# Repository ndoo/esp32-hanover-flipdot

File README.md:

# ESP32 Hanover Flip-dot Sign Controller

This controller directly controls Hanover Displays Ltd. dot-boards CMOS logic hardware directly through the parallel 14-pin ribbon cable, without the Hanover 7070 or 7080 processor board.

## Design Considerations

This controller's design is based on [Damien Walsh's work on Hanover flip-dot signs](https://damow.net/fun-with-flip-dot-displays/), with only layout changes targeting PCB fabrication and assembly services.

The following considerations went into the PCB schematic and layout:

* SMT components used where possible
* All components are only on the top side of the PCB
* The ESP32-PICO-D4 SIP is used instead of a separate ESP32 module
* PCB size minimized to increase savings with panelization
* All board enable lines are connected to support up to 4 parallel dot-boards
* Generous use of ground stitching vias

## PCBA Notes

### Time/Money Saving

I strongly suggest removing the following items from the PCBA BoM, as they are generic 2.54mm through-hole parts and can be easily sourced at a local dealer:

* J2: CONN HEADER R/A 14POS 2.54MM
* J3: DIP Black Male Header VERT

### Dot-board Ribbon Cable

J2 is specified as a 2x7 pin 2.54mm pitch shrouded header for IDC cables, so a matching 2x7 pin 2.54mm pitch IDC connector must be retrofitted on the original Hanover dot-board ribbon cable.

The original Hanover cable is a Lumberg Micromodul series MICA 14 connector which mates to a corresponding MICS 14 header. As the Lumberg Micromodul parts are much harder to source (with the bottom line being that they cost more) and requires a custom footprint on the PCB, a jellybean part solution was preferred.

### Bill of Materials

The BOM CSV provided uses [Seeed Studio OPL](https://www.seeedstudio.com/opl.html) SKUs for jellybean parts as I have a personal preference for Seeed Studio's Fusion PCBA service. If using other PCBA services, please substitute the Seeed OPL SKUs accordingly.

## Firmware

Reference ESP32 Arduino framework firmware source is available at [ndoo/esp32-hanover-flipdot-firmware](https://github.com/ndoo/esp32-hanover-flipdot-firmware)

### ESP32 GPIO mapping

* Enable Display 1 - GPIO 15
* Enable Display 2 - GPIO 13
* Enable Display 3 - GPIO 12
* Enable Display 4 - GPIO 14
* Column Advance - GPIO 27
* Reset - GPIO 26
* Set/Unset - GPIO 25
* Row Advance - GPIO 33
* Coil Pulse - GPIO 2
* LED 1 - GPIO 23
* LED 2 - GPIO 19
* LED 3 - GPIO 22

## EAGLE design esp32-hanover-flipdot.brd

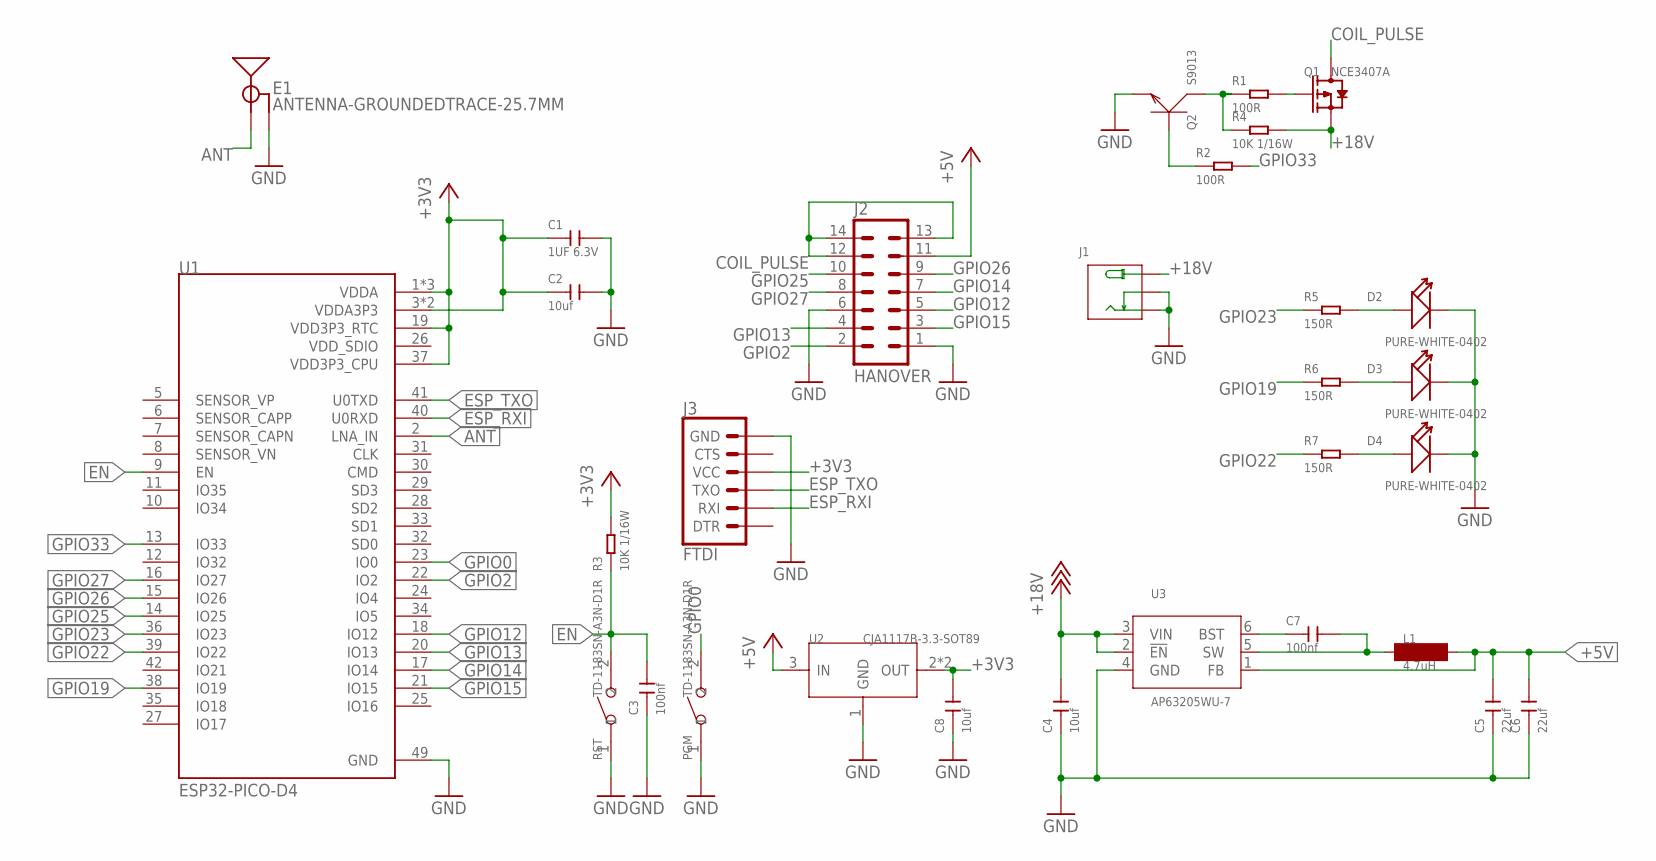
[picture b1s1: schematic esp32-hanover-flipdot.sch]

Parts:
C1: 1UF 6.3V; C0402
C2, C8: 10uf; C0402
C3, C7: 100nf; C0402
C4: 10uf; C0805
C5, C6: 22uf; C0805
D2, D3, D4: PURE-WHITE-0402; LED-0402
E1: ANTENNA-GROUNDEDTRACE-25.7MM; TRACE_ANTENNA_2.4GHZ_25.7MM
J1: DC-005; 3P-L14.2*W11.0*H9.0MM
J2: HANOVER; ML14
J3: FTDI; 6_PIN_SERIAL_TARGET_SIDE_W_SILK
L1: 4.7uH; INDC2016X100N
PGM: TD-1183SN-A3N-D1R; SW2-2.6-3.0X2.5X1.2+0.4MM
Q1: NCE3407A; SOT-23
Q2: S9013; SOT-23
R1, R2: 100R; R0402
R3, R4: 10K 1/16W; R0402
R5, R6, R7: 150R; R0402; MPN RC0402FR-07150RL
RST: TD-1183SN-A3N-D1R; SW2-2.6-3.0X2.5X1.2+0.4MM
U1: ESP32-PICO-D4; PQFN50P700X700X104-49N
U2: CJA1117B-3.3-SOT89; SOT-89
U3: AP63205WU-7; SOT95P280X100-6N

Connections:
+3V3: C1.1, C2.1, C8.2, J3.P$4 (VCC), R3.2, U1.1 (VDDA), U1.3 (VDDA3P3), U1.4 (VDDA3P3), U1.19 (VDD3P3_RTC), U1.37 (VDD3P3_CPU), U1.43 (VDDA), U1.46 (VDDA), U2.2 (OUT), U2.4 (OUT)
+5V: C5.2, C6.2, J2.11, L1.2, U2.3 (IN), U3.1 (FB)
+18V: C4.2, J1.+B (+), J1.+T (+), Q1.2 (S), R4.2, U3.2 (!EN), U3.3 (VIN)
ANT: E1.ANT (SIGNAL), U1.2 (LNA_IN)
COIL_PULSE: J2.12, J2.13, J2.14, Q1.3 (D)
EN: C3.2, R3.1, RST.2, U1.9 (EN)
ESP_RXI: J3.P$3 (RXI), U1.40 (U0RXD)
ESP_TXO: J3.P$2 (TXO), U1.41 (U0TXD)
GND: C1.2, C2.2, C3.1, C4.1, C5.1, C6.1, C8.1, D2.-, D3.-, D4.-, E1.GND, E1.GND2 (GND), J1.-1B (-), J1.-1T (-), J1.-2B (CDN), J1.-2T (CDN), J2.1, J2.6, J3.P$6 (GND), PGM.1, Q2.2 (E), RST.1, U1.49 (GND), U2.1 (GND), U3.4 (GND)
GPIO0: PGM.2, U1.23 (IO0)
GPIO2: J2.2, U1.22 (IO2)
GPIO12: J2.5, U1.18 (IO12)
GPIO13: J2.4, U1.20 (IO13)
GPIO14: J2.7, U1.17 (IO14)
GPIO15: J2.3, U1.21 (IO15)
GPIO19: R6.1, U1.38 (IO19)
GPIO22: R7.1, U1.39 (IO22)
GPIO23: R5.1, U1.36 (IO23)
GPIO25: J2.10, U1.14 (IO25)
GPIO26: J2.9, U1.15 (IO26)
GPIO27: J2.8, U1.16 (IO27)
GPIO33: R2.2, U1.13 (IO33)
unnamed: Q1.1 (G), R1.2
unnamed: Q2.3 (C), R1.1, R4.1
unnamed: Q2.1 (B), R2.1
unnamed: C7.1, U3.6 (BST)
unnamed: D2.+, R5.2
unnamed: D3.+, R6.2
unnamed: D4.+, R7.2
unnamed: C7.2, L1.1, U3.5 (SW)
VDD_SDIO: U1.26 (VDD_SDIO)

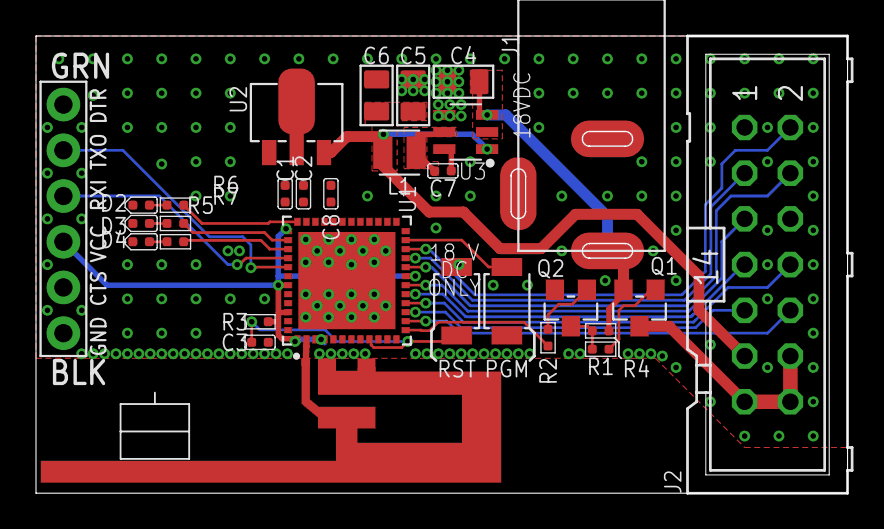
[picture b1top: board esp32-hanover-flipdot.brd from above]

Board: 2 copper layers, 45.1 x 25.4 mm, 30 parts (0 on the bottom side), 30 nets.

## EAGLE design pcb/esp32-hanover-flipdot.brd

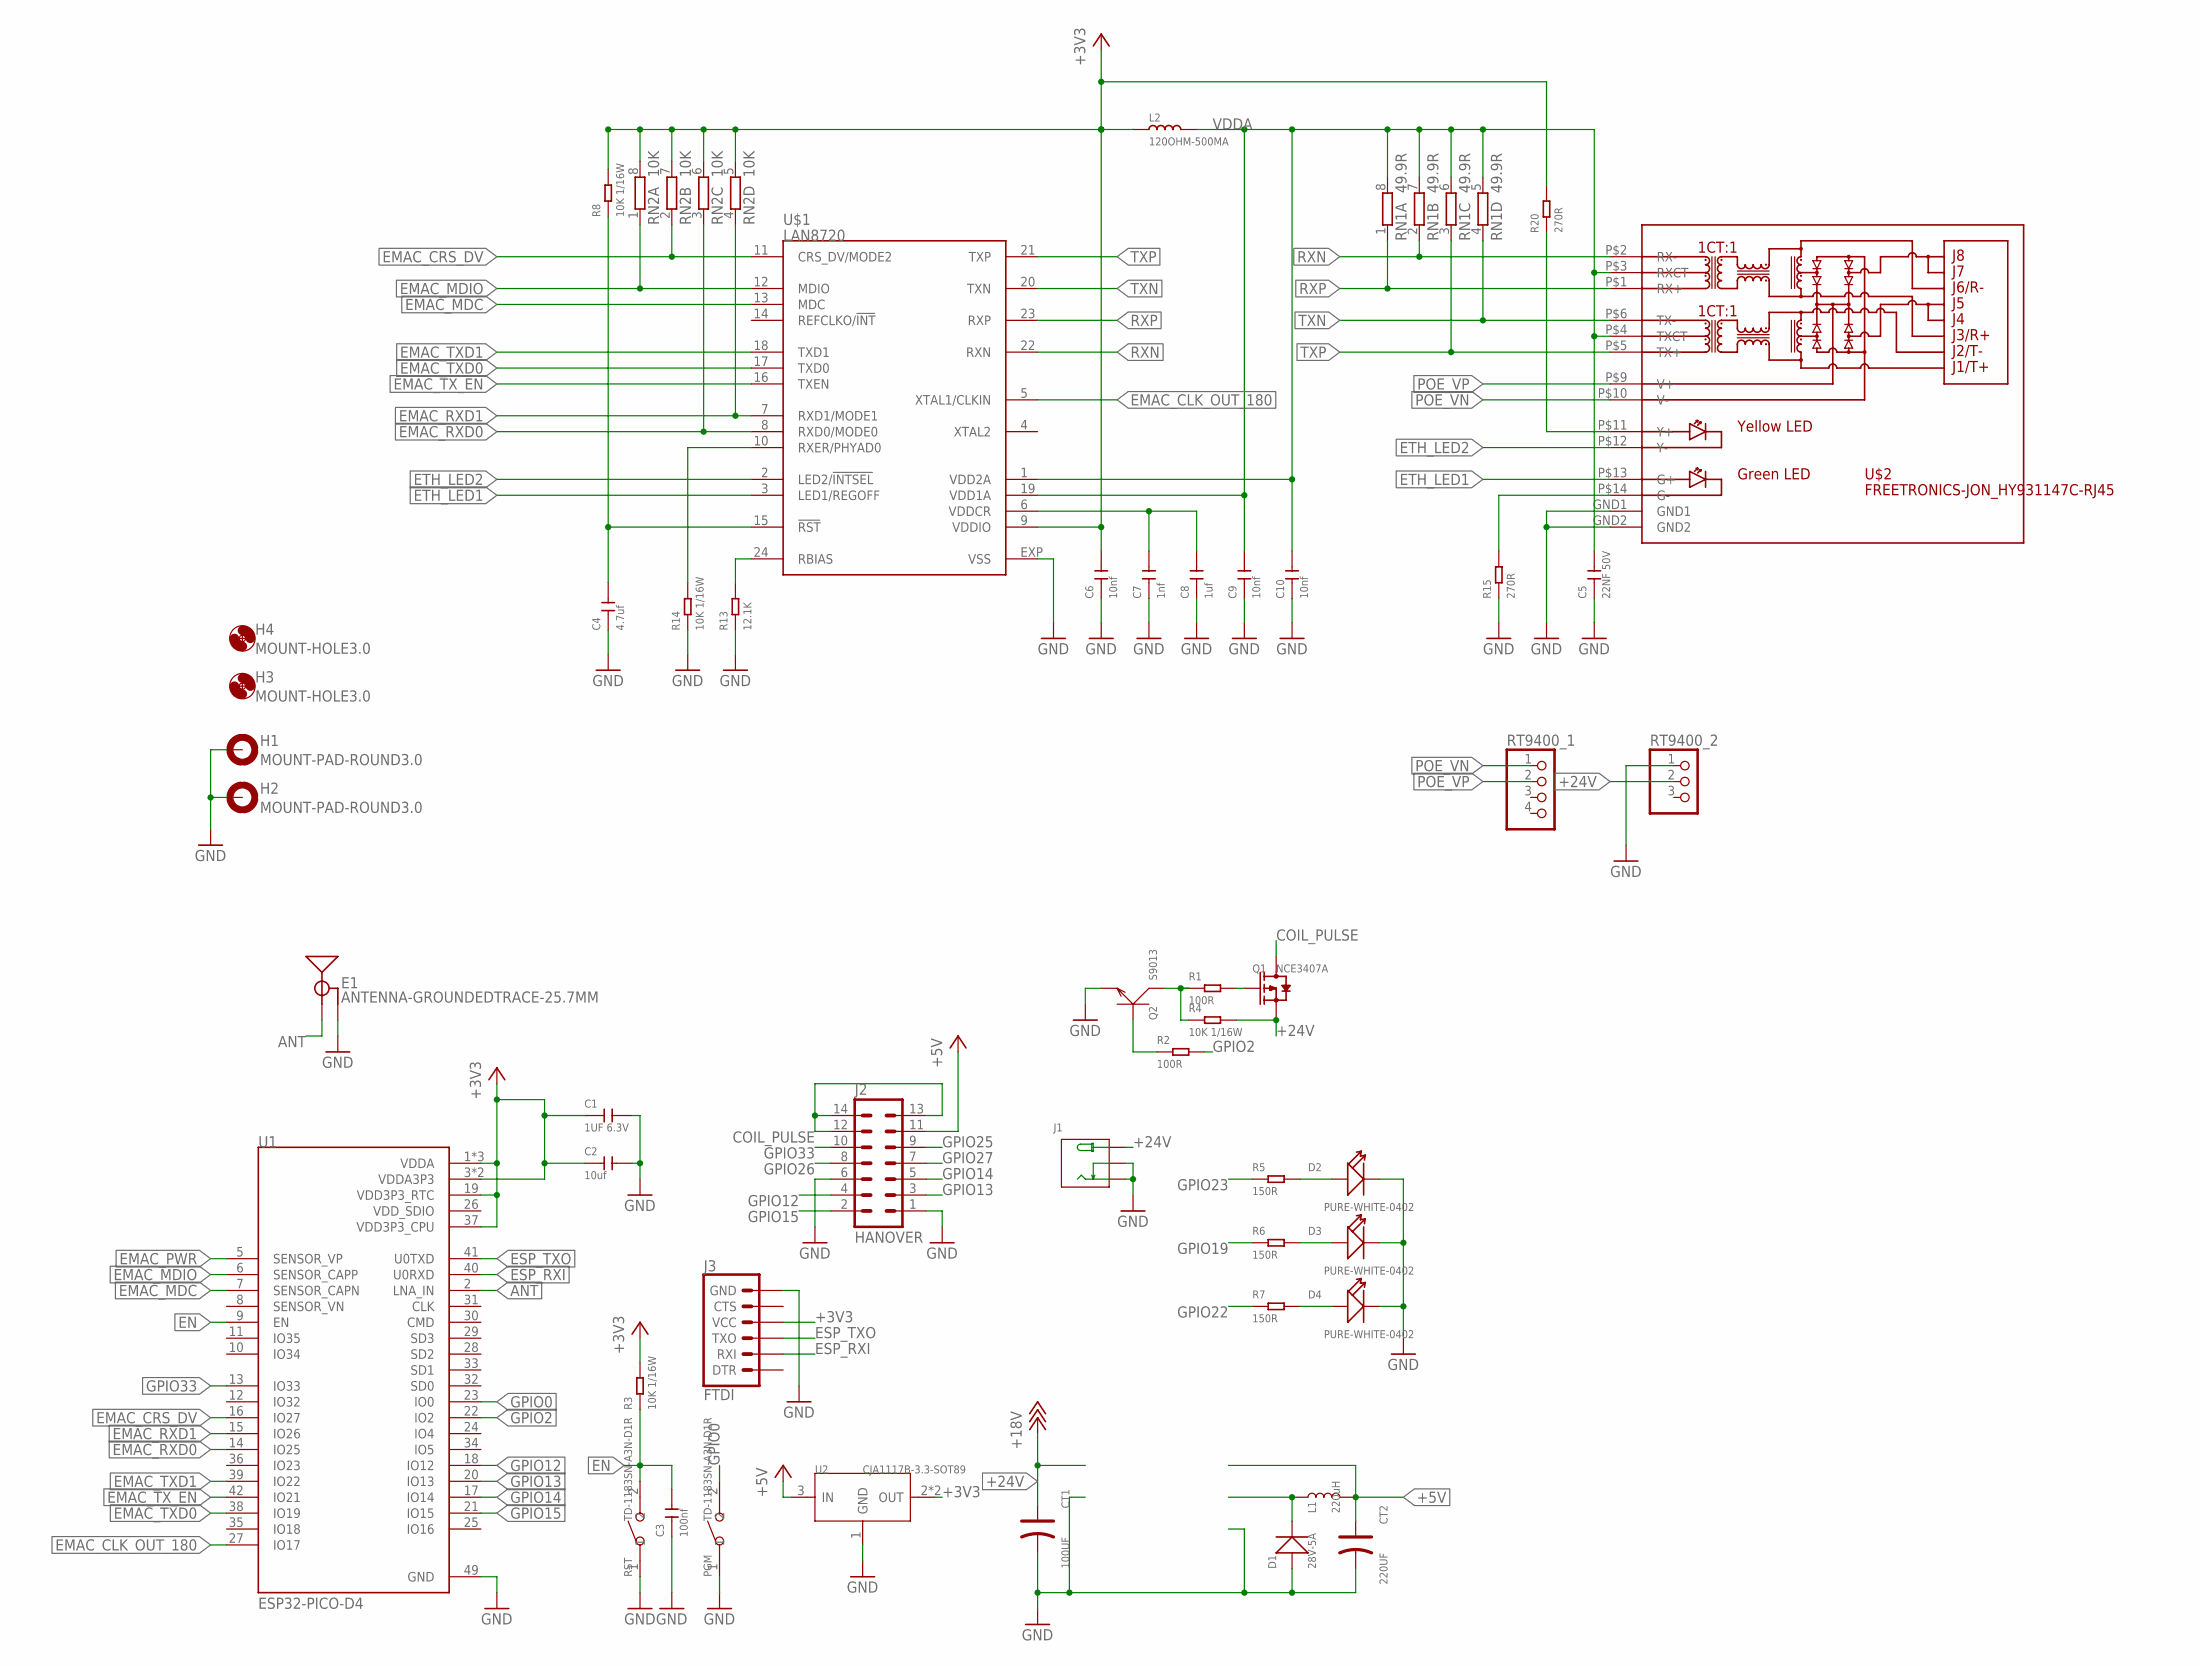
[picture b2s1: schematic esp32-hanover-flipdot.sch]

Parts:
C1: 1UF 6.3V; C0402
C2: 10uf; C0402
C3: 100nf; C0402
C4: 4.7uf; C0402
C5: 22NF 50V; C0402
C6, C9, C10: 10nf; C0402
C7: 1nf; C0402
C8: 1uf; C0402
CT1: 100UF; ELECTRO-SMD-C-6MM; MPN 302030000
CT2: 220UF; ELECTRO-SMD-C-6MM
D1: 28V-5A; DO-214AA
D2, D3, D4: PURE-WHITE-0402; LED-0402
E1: ANTENNA-GROUNDEDTRACE-25.7MM; TRACE_ANTENNA_2.4GHZ_25.7MM
H1, H2: MOUNT-PAD-ROUND3.0; 3,0-PAD
H3, H4: MOUNT-HOLE3.0; 3,0
J1: DC-005; 3P-L14.2*W11.0*H9.0MM
J2: HANOVER; ML14
J3: FTDI; 6_PIN_SERIAL_TARGET_SIDE_W_SILK
L1: 220uH; CR54
L2: 120OHM-500MA; L0603
PGM: TD-1183SN-A3N-D1R; SW2-2.6-3.0X2.5X1.2+0.4MM
Q1: NCE3407A; SOT-23
Q2: S9013; SOT-23
R1, R2: 100R; R0402
R3, R4, R8, R14: 10K 1/16W; R0402
R5, R6, R7: 150R; R0402; MPN RC0402FR-07150RL
R13: 12.1K; R0402
R15, R20: 270R; R0402
RN1: 49.9R; YC124; MPN YC124-FR-0749R9L
RN2: 10K; YC124; MPN YC124-FR-0710KL
RST: TD-1183SN-A3N-D1R; SW2-2.6-3.0X2.5X1.2+0.4MM
RT9400_1: PINHD-1X4; 1X04
RT9400_2: PINHD-1X3; 1X03
U1: ESP32-PICO-D4; PQFN50P700X700X104-49N
U2: CJA1117B-3.3-SOT89; SOT-89
U$1: LAN8720; QFN24
U$2: FREETRONICS-JON_HY931147C-RJ45; FREETRONICS-JON_HY931147C

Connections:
+3V3: C1.1, C2.1, C6.2, J3.P$4 (VCC), L2.1, R3.2, R8.2, R20.2, RN2.5 (2), RN2.6 (2), RN2.7 (2), RN2.8 (2), U1.1 (VDDA), U1.3 (VDDA3P3), U1.4 (VDDA3P3), U1.19 (VDD3P3_RTC), U1.37 (VDD3P3_CPU), U1.43 (VDDA), U1.46 (VDDA), U2.2 (OUT), U2.4 (OUT), U$1.9 (VDDIO)
+5V: CT2.+, J2.11, L1.P$2 (2), U2.3 (IN)
+24V: CT1.+, J1.+B (+), J1.+T (+), Q1.2 (S), R4.2, RT9400_2.2
ANT: E1.ANT (SIGNAL), U1.2 (LNA_IN)
COIL_PULSE: J2.12, J2.13, J2.14, Q1.3 (D)
EMAC_CLK_OUT_180: U1.27 (IO17), U$1.5 (XTAL1/CLKIN)
EMAC_CRS_DV: RN2.2 (1), U1.16 (IO27), U$1.11 (CRS_DV/MODE2)
EMAC_MDC: U1.7 (SENSOR_CAPN), U$1.13 (MDC)
EMAC_MDIO: RN2.1, U1.6 (SENSOR_CAPP), U$1.12 (MDIO)
EMAC_PWR: U1.5 (SENSOR_VP)
EMAC_RXD0: RN2.3 (1), U1.14 (IO25), U$1.8 (RXD0/MODE0)
EMAC_RXD1: RN2.4 (1), U1.15 (IO26), U$1.7 (RXD1/MODE1)
EMAC_TXD0: U1.38 (IO19), U$1.17 (TXD0)
EMAC_TXD1: U1.39 (IO22), U$1.18 (TXD1)
EMAC_TX_EN: U1.42 (IO21), U$1.16 (TXEN)
EN: C3.2, R3.1, RST.2, U1.9 (EN)
ESP_RXI: J3.P$3 (RXI), U1.40 (U0RXD)
ESP_TXO: J3.P$2 (TXO), U1.41 (U0TXD)
ETH_LED1: U$1.3 (LED1/REGOFF), U$2.P$13 (G+)
ETH_LED2: U$1.2 (LED2/!INTSEL), U$2.P$12 (Y-)
GND: C1.2, C2.2, C3.1, C4.1, C5.1, C6.1, C7.1, C8.1, C9.1, C10.1, CT1.-, CT2.-, D1.+, D2.-, D3.-, D4.-, E1.GND, E1.GND2 (GND), H1.B3,0, H2.B3,0, J1.-1B (-), J1.-1T (-), J1.-2B (CDN), J1.-2T (CDN), J2.1, J2.6, J3.P$6 (GND), PGM.1, Q2.2 (E), R13.1, R14.1, R15.1, RST.1, RT9400_2.1, U1.49 (GND), U2.1 (GND), U$1.EXP (VSS), U$2.GND1, U$2.GND2
GPIO0: PGM.2, U1.23 (IO0)
GPIO2: R2.2, U1.22 (IO2)
GPIO12: J2.4, U1.18 (IO12)
GPIO13: J2.3, U1.20 (IO13)
GPIO14: J2.5, U1.17 (IO14)
GPIO15: J2.2, U1.21 (IO15)
GPIO19: R6.1
GPIO22: R7.1
GPIO23: R5.1
GPIO25: J2.9
GPIO26: J2.8
GPIO27: J2.7
GPIO33: J2.10, U1.13 (IO33)
unnamed: Q1.1 (G), R1.2
unnamed: Q2.3 (C), R1.1, R4.1
unnamed: Q2.1 (B), R2.1
unnamed: D1.-, L1.P$1 (1)
unnamed: D2.+, R5.2
unnamed: D3.+, R6.2
unnamed: D4.+, R7.2
unnamed: R14.2, U$1.10 (RXER/PHYAD0)
unnamed: R13.2, U$1.24 (RBIAS)
unnamed: R15.2, U$2.P$14 (G-)
unnamed: C7.2, C8.2, U$1.6 (VDDCR)
unnamed: R20.1, U$2.P$11 (Y+)
unnamed: C4.2, R8.1, U$1.15 (!RST)
POE_VN: RT9400_1.1, U$2.P$10 (V-)
POE_VP: RT9400_1.2, U$2.P$9 (V+)
RXN: RN1.2 (1), U$1.22 (RXN), U$2.P$2 (RX-)
RXP: RN1.1, U$1.23 (RXP), U$2.P$1 (RX+)
TXN: RN1.4 (1), U$1.20 (TXN), U$2.P$6 (TX-)
TXP: RN1.3 (1), U$1.21 (TXP), U$2.P$5 (TX+)
VDDA: C5.2, C9.2, C10.2, L2.2, RN1.5 (2), RN1.6 (2), RN1.7 (2), RN1.8 (2), U$1.1 (VDD2A), U$1.19 (VDD1A), U$2.P$3 (RXCT), U$2.P$4 (TXCT)
VDD_SDIO: U1.26 (VDD_SDIO)

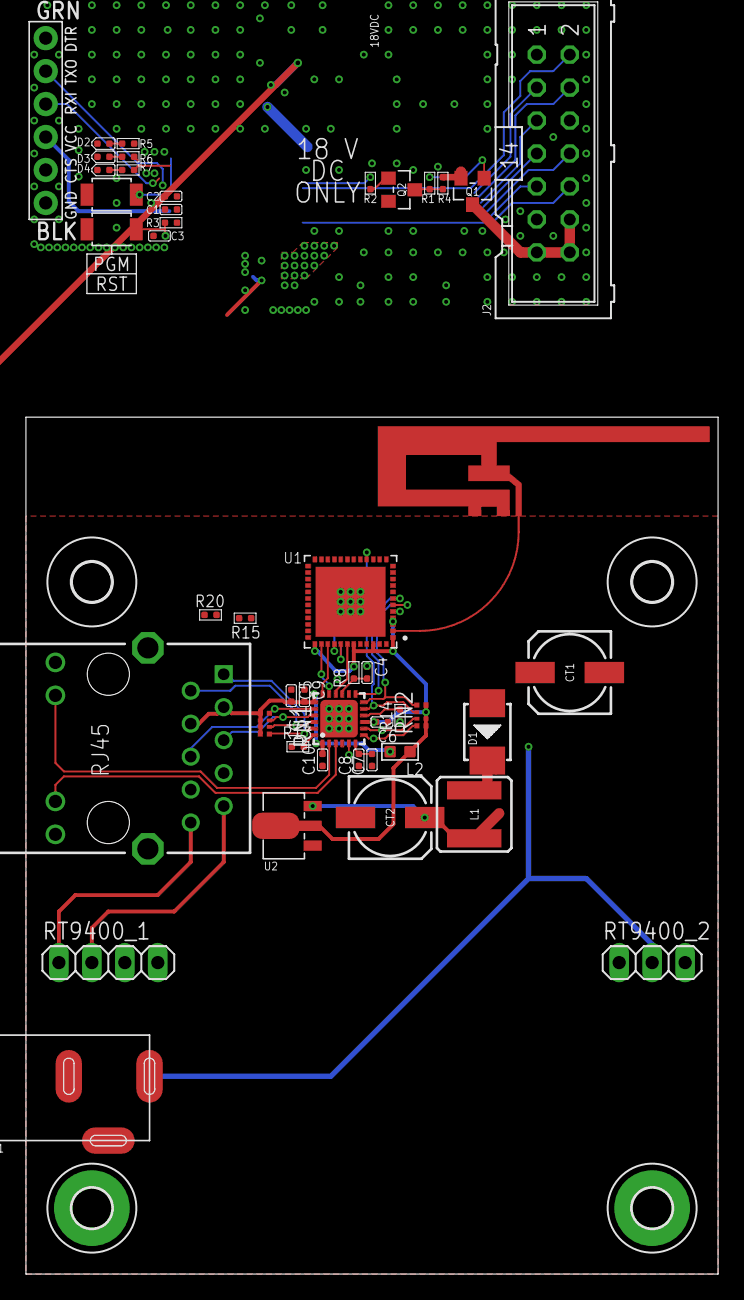
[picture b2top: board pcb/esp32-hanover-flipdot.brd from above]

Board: 2 copper layers, 53.3 x 66.0 mm, 50 parts (0 on the bottom side), 47 nets.

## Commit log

2020-05-17 pcb: Add Ethernet and PoE
2020-05-17 Clean up non-PCB files to be migrated to a fork of the repository
2020-05-18 Change buck converter from LM7576-5.0 to AP63205, change antenna
    Change buck converter from LM7576-5.0 to AP63205, which uses drastically less space and switches at a higher frequency thus requiring smaller passives, and does not require a schottky diode.
    Change antenna to a larger inverted-F antenna which has more isotropic gain thus makes placement of the board less of a factor in Wi-Fi performance.

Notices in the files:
parts and their libraries:
SparkFun-Connectors: Licensing: Creative Commons ShareAlike 4.0 International - https://creativecommons.org/licenses/by-sa/4.0
microchip-smsc-lan8720: (C) 2014 Tomasz Boleslaw CEDRO, cederom@tlen.pl, http://www.tomek.cedro.info.
